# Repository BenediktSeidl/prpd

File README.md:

# prpd

prpd is a software and hardware solution to make monitoring information from the
NEDAP PowerRouter available although their cloud service was shot down
at 2021-01-31.

The Methods were tested with NEDAP PowerRouter `PR37Bi` Version `7.1.2`.

## Status of this project

I had this running for some time and it worked fine, but unfortunately the
Battery of the PowerRouter broke and the PowerRouter does not support current
Batteries, so the whole System was replaced, and I have no longer a system to
test with.

## Getting the data from the PowerRouter

### HTTP

The PowerRouter normally sends monitoring data every minute via a HTTP-POST
request to `logging1.PowerRouter.com`. This is done without any encryption, so
we can simple bend the network traffic into our direction and read the data.

[More Information](doc/http.md)

### RS485

Some of the data is collected via a RS485 interface of EM24 Energy Sensors by
Carlo Gavazzi. This data is transfered about every second. As the PowerRouter
is already a master on the bus we don't want to disturb any communication and
simple tap into the data lines and listen to the communication.

[More Information](doc/serial.md)

#### Hardware

In order to tab into the RS485 lines, one could access the EM24 Sensors and add
some wires there, but the Sensors are in the fuse box and one doesn't mess with
this one normally.

There is also the need for additional hardware because most of the linux boards
don't support RS485 out of the box. A normal RS485 USB-dongle may be used.

On the other hand, most linux boards do have UART exposed on some headers, so
we can add a UART - RS485 transceiver. The SP3485 has also the handy feature
that it can be configured in a way that it is not possible to write to the
RS485 bus, an ideal feature for our application.

[More Information](hardware/README.md)

## Use the data from the PowerRouter

prpw is written in a way that it should be possible to add you favourite
output. Currently the following outputs are available:

### MQTT Home Assistant

Outputs the data on MQTT so it is possible for Home Assistant to auto discover
all available Data.

### OpenWB

Output the data on MQTT so OpenWB can read the data. This is not done yet, but
will be definitely implemented in the near future.

### Prometheus

With this output it's possible to scrape the data with prometheus.

## Configuration

Configuration is done via environment variables.

* `PRPD_ACTION`: how to obtain the data. either `serial` or `http`. If you want
  to get data from http and serial, you have to run the programm twice.
* `PRPD_OUTPUT_HASS_ACTIVE`: `1` if you want to activate the homeassistant output
* `PRPD_OUTPUT_HASS_MQTT_URI`: mqtt broker for homeassistant output, defaults to
  `tcp://localhost:1883`
* `PRPD_OUTPUT_PROM_ACTIVE`: `1` if you want to activate the prometheus output
* `PRPD_OUTPUT_PROM_PORT`: sets the port of the prometheus output. If you want
  to run serial and http in parallel, you have to specify two different ports
  and configure two differen datasources. in prometheus.
* `PRPD_SERIAL_PORT`: serial port (like `/dev/ttyUSB0`) where to listen for
  data

## Development

### Installing rust and build dependencies

```
# installing rustup
curl --proto '=https' --tlsv1.2 -sSf https://sh.rustup.rs | sh # https://www.rust-lang.org/tools/install
source $HOME/.cargo/env
rustup toolchain install nightly
rustup default nightly
# installing build dependencies
apt-get install pkg-config libudev-dev cmake
# install target support (only if you want to run this on GL-AR150)
rustup target add mips-unknown-linux-musl
# installing tool to compress executable (only if you want to run this on GL-AR150)
apt-get install upx
```

### Testing locally

```bash
bash dev/run_http.sh # to start the http server
bash dev/http_post_log.sh # to send some test data to the server

bash dev/serial_socat.sh # to create a virtual serial port
bash dev/run_serial.sh # to start prpd in serial mode
python3 dev/serial_write_data.py # to send data to virtual serial port
```

## GL-AR150

GL-AR150 is a cheap, low power network device that can be used as a platform
for prpd. The idea is to use a low power device to gather the data and then
send it to a more powerful device in order to store the data.

[More Information](hardware/GL-AR150.md)

## Disclaimer

Use at your own risk!

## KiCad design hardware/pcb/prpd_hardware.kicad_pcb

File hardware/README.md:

# prpd hardware

The pcb is designed in a way so it's easy to change the tapping into the 8 data
lines of the CAT cable, just in case...

## Components

* 1x [SP3485 SO-8](https://www.reichelt.de/-p166271.html)
* 1x [0805 100nF](https://www.reichelt.de/-p31879.html)
* 2x [RJ45 Jack](https://www.reichelt.de/-p257581.html) Weidmüller 1455240000

## Images

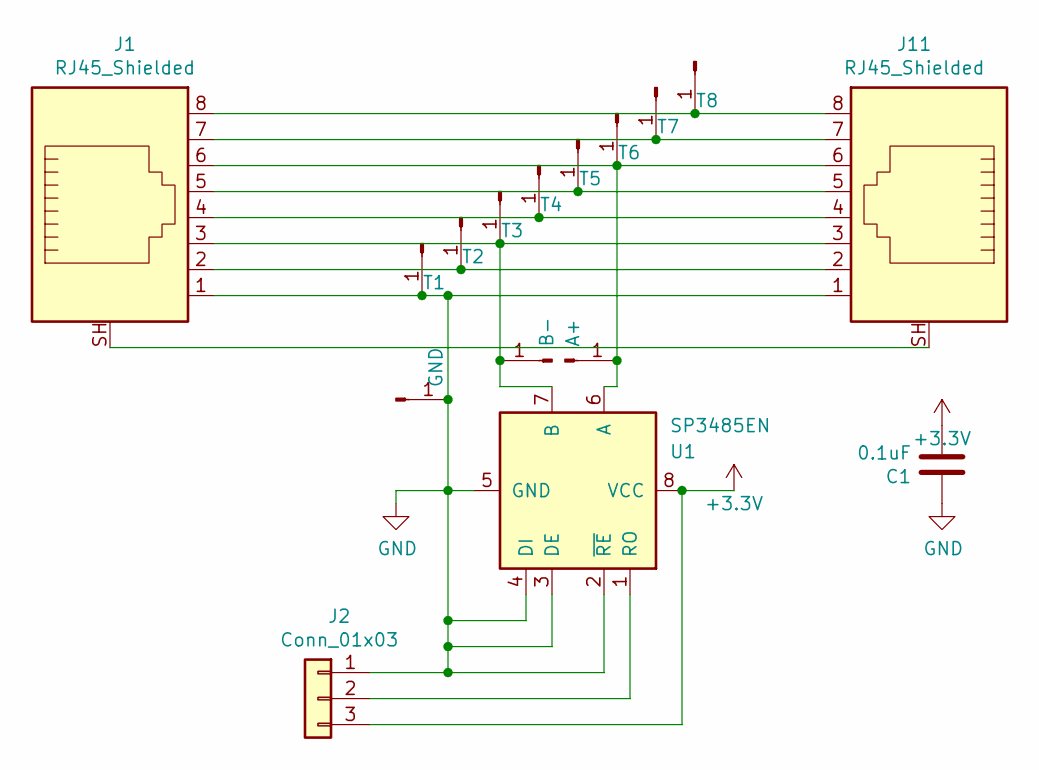
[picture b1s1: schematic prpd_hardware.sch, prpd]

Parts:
C1: 0.1uF; C_0805_2012Metric
J1, J11: RJ45_Shielded; CAT5 T1U 2.8N4N
J2: Conn_01x03; JST_XH_B3B-XH-A_1x03_P2.50mm_Vertical
T1, T2, T3, T4, T5, T6, T7, T8: tab
TI1: GND; tab
TI2: A+; tab
TI3: B-; tab
U1: SP3485EN; SOIC-8_3.9x4.9mm_P1.27mm

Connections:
+3V3: C1.2, J2.3, U1.8 (VCC)
GND: C1.1, J1.1, J2.1, J11.1, T1.1, TI1.1, U1.2 (~RE~), U1.3 (DE), U1.4 (DI), U1.5 (GND)
unnamed: J1.2, J11.2, T2.1
unnamed: J1.3, J11.3, T3.1, TI3.1, U1.7 (B)
unnamed: J1.4, J11.4, T4.1
unnamed: J1.5, J11.5, T5.1
unnamed: J1.6, J11.6, T6.1, TI2.1, U1.6 (A)
unnamed: J1.7, J11.7, T7.1
unnamed: J1.8, J11.8, T8.1
unnamed: J1.SH, J11.SH
unnamed: J2.2, U1.1 (RO)

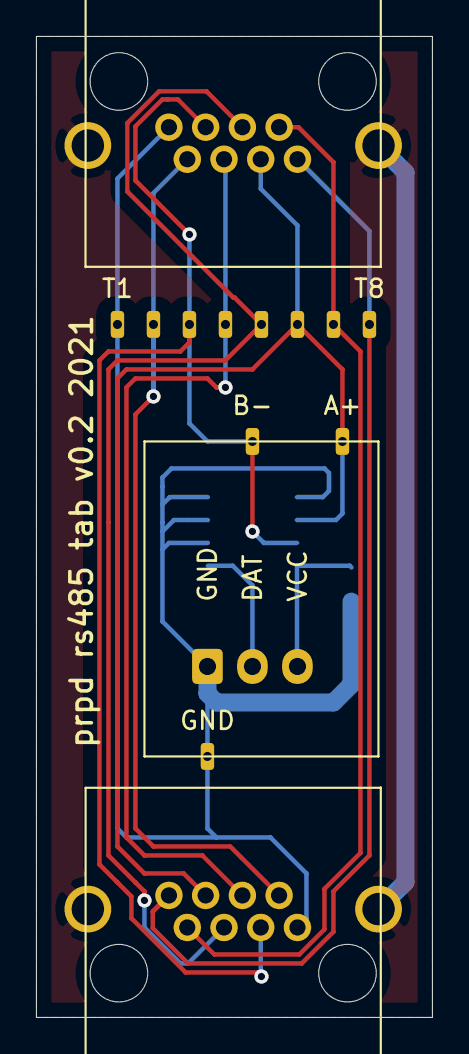
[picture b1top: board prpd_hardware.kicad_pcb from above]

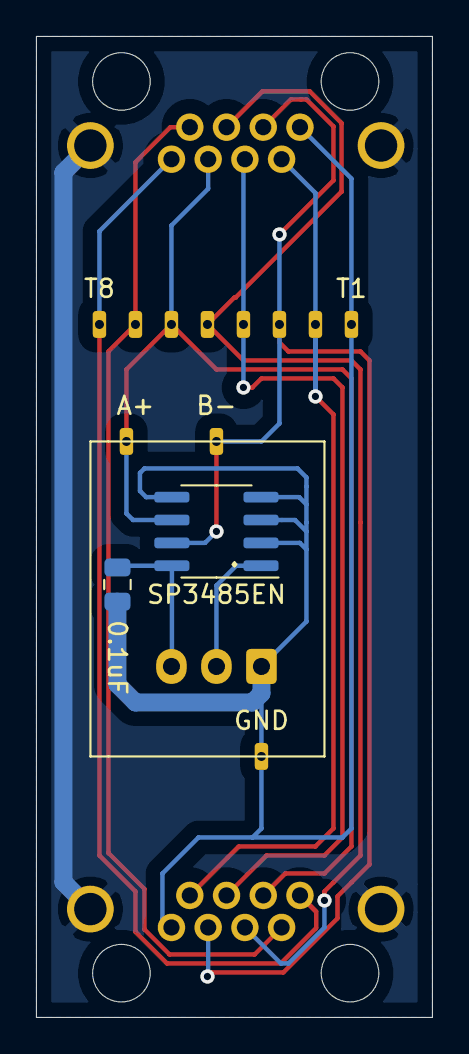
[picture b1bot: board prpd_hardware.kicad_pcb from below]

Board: 2 copper layers, 22.0 x 54.5 mm, 16 parts (2 on the bottom side), 11 nets.

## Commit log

2021-01-25 change output interface to support other than mqtt
2021-01-26 add docs how to build prpd
2021-01-27 add prometheus data output
2021-01-27 replace hass device_class by own data structure
2021-01-27 add and document config
2021-01-28 serial addresses are in words (2 bytes) not bytes
2021-01-28 whitespace is not ignored (?) bind to 0.0.0.0
2021-01-28 fix data model: missing unit
2021-01-28 remove prometheus dependency
    AtomicU64 not available in mips-unknown-linux-musl
    https://github.com/tikv/rust-prometheus/issues/315
2021-01-28 cargo fmt
2021-01-28 hardware: add power symbols and screenshots
2021-01-28 add docs about gl-ar150 setup
2021-01-28 describe different output formats
2021-01-28 add reconnection support for mqtt
2021-02-03 todo was resolved with 94c2cd1e128916fcc9c6855072
2021-02-07 add pictures of hardware and restructure README.md
2021-02-13 fix config in dev scripts
2021-02-13 add logging
2021-02-13 add openwrt config to restart more often
2021-02-13 optimize for smaller binary size
    before logging ~3.7MB, after ~4.2MB, now 1.9MB, thanks upx!
2021-02-19 fix mixup of datalines
    datalines of transceivers do swap A and B. the relevant information is
    +/- or non inverting/inverting. serial ttl output was inverted; readings
    where broken, most symbols where around 255.
2021-02-23 add paragraph about serial console on openwrt
2021-08-28 status update
